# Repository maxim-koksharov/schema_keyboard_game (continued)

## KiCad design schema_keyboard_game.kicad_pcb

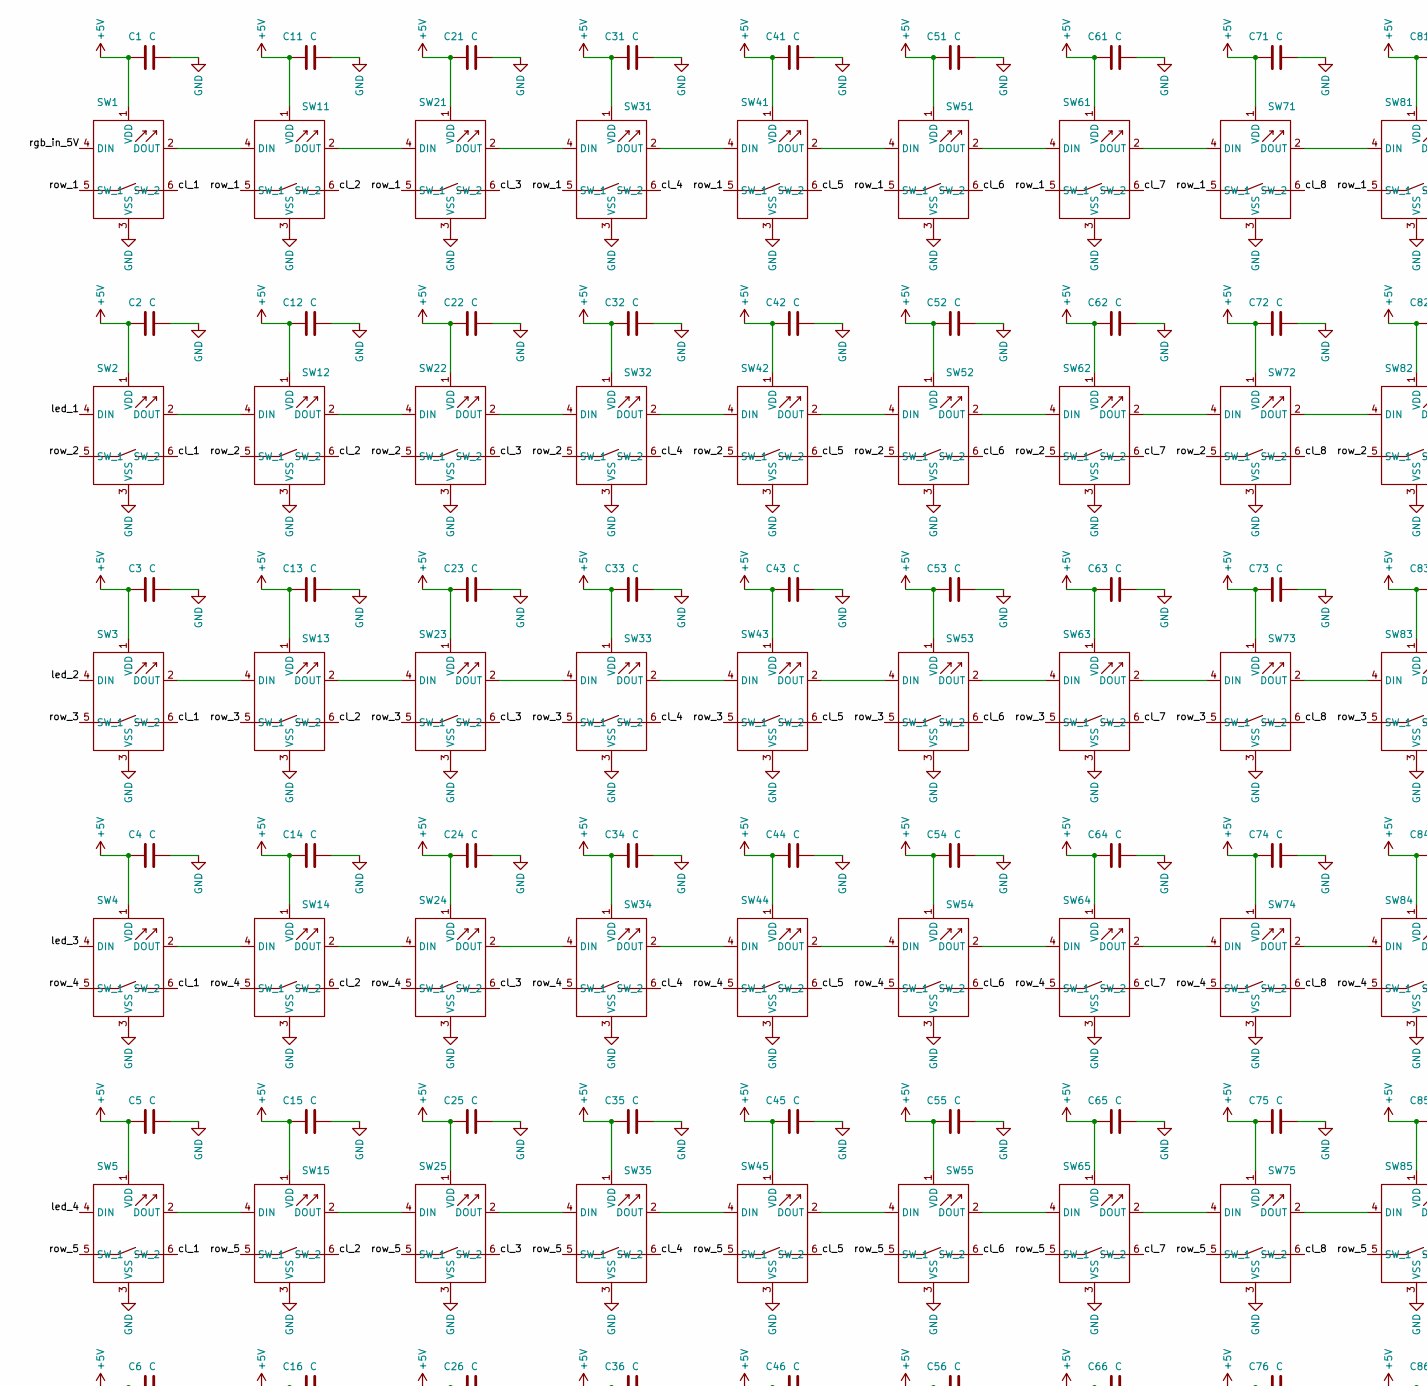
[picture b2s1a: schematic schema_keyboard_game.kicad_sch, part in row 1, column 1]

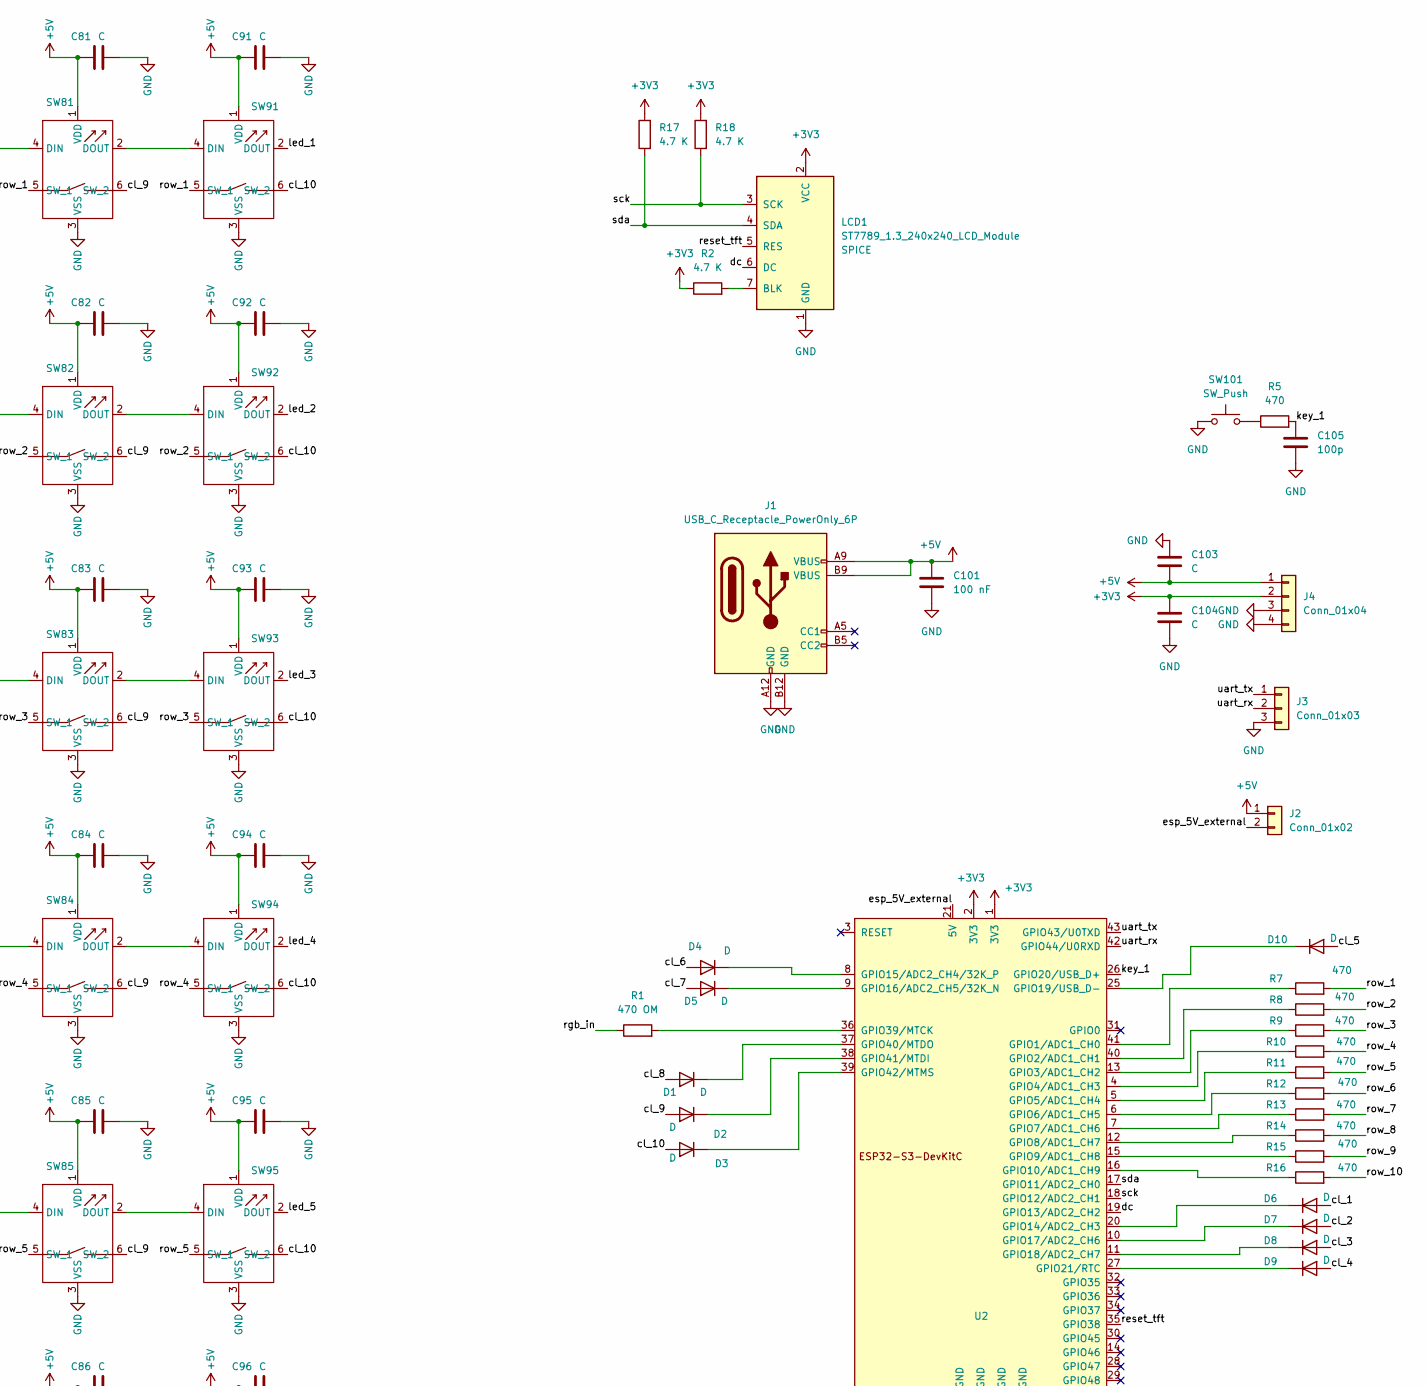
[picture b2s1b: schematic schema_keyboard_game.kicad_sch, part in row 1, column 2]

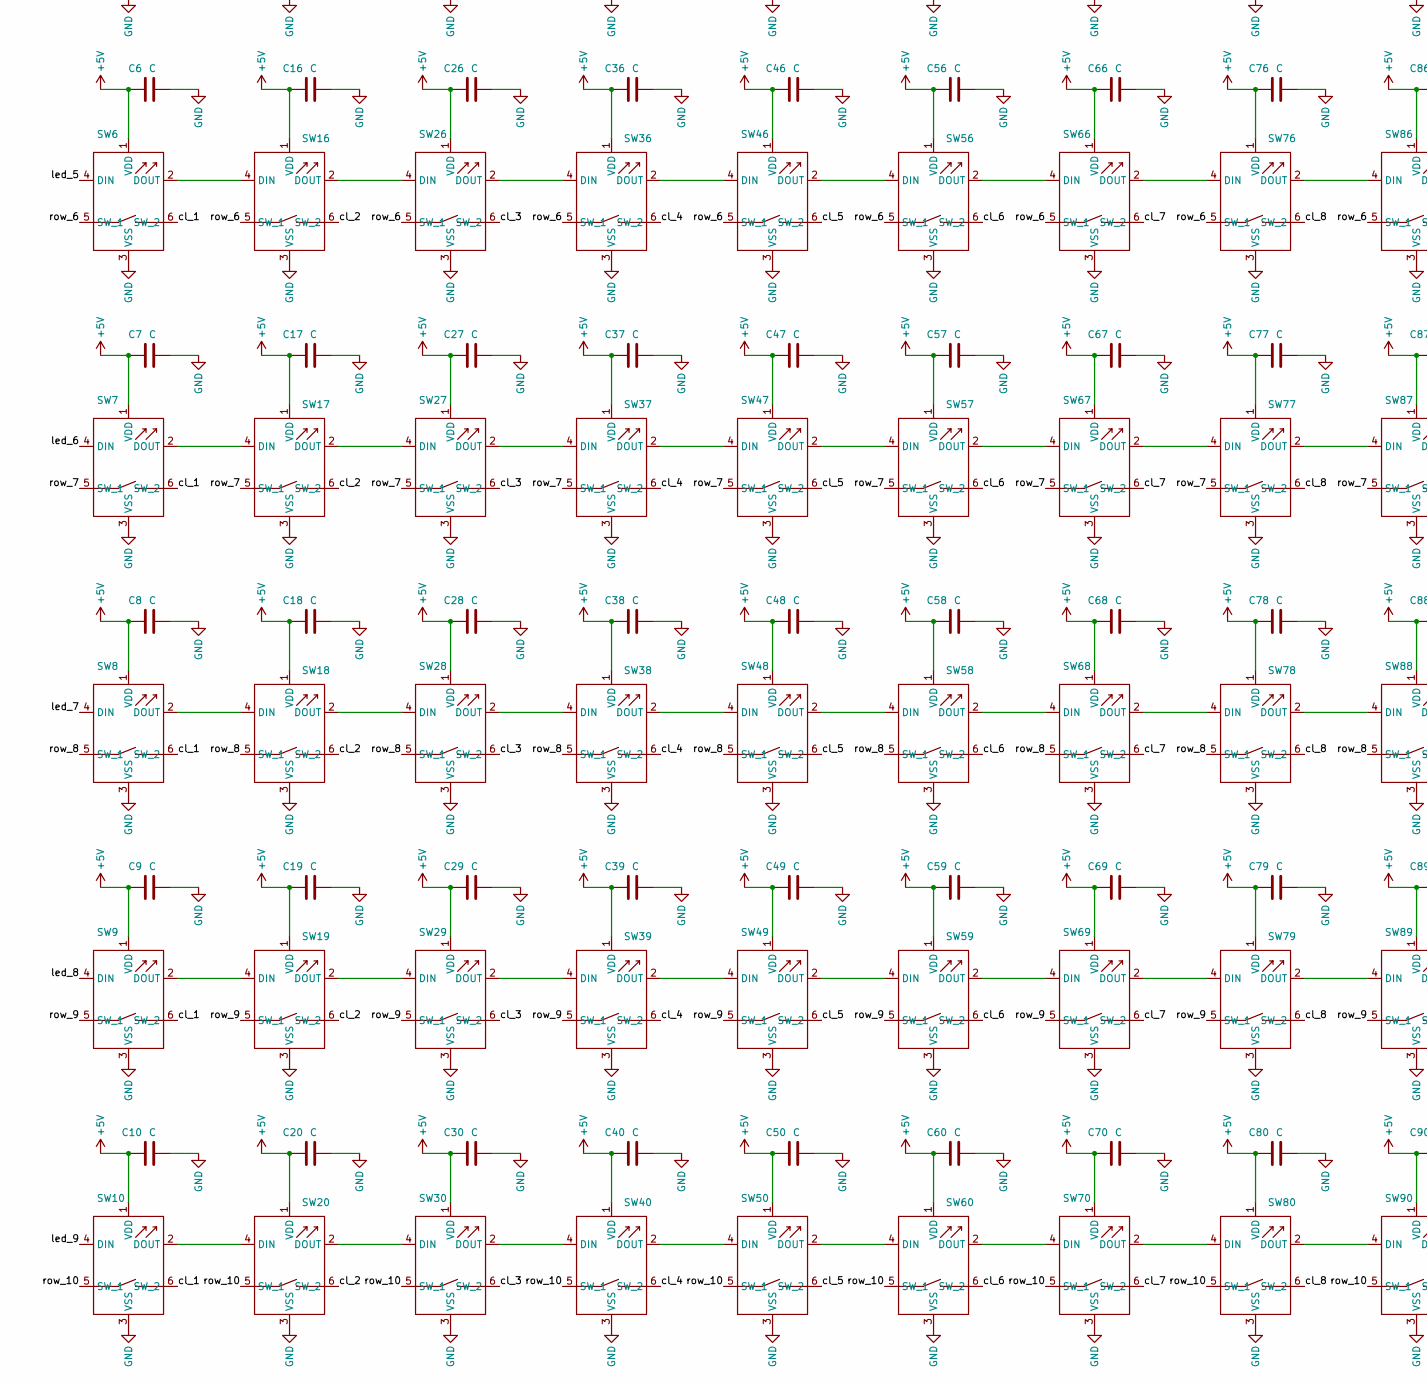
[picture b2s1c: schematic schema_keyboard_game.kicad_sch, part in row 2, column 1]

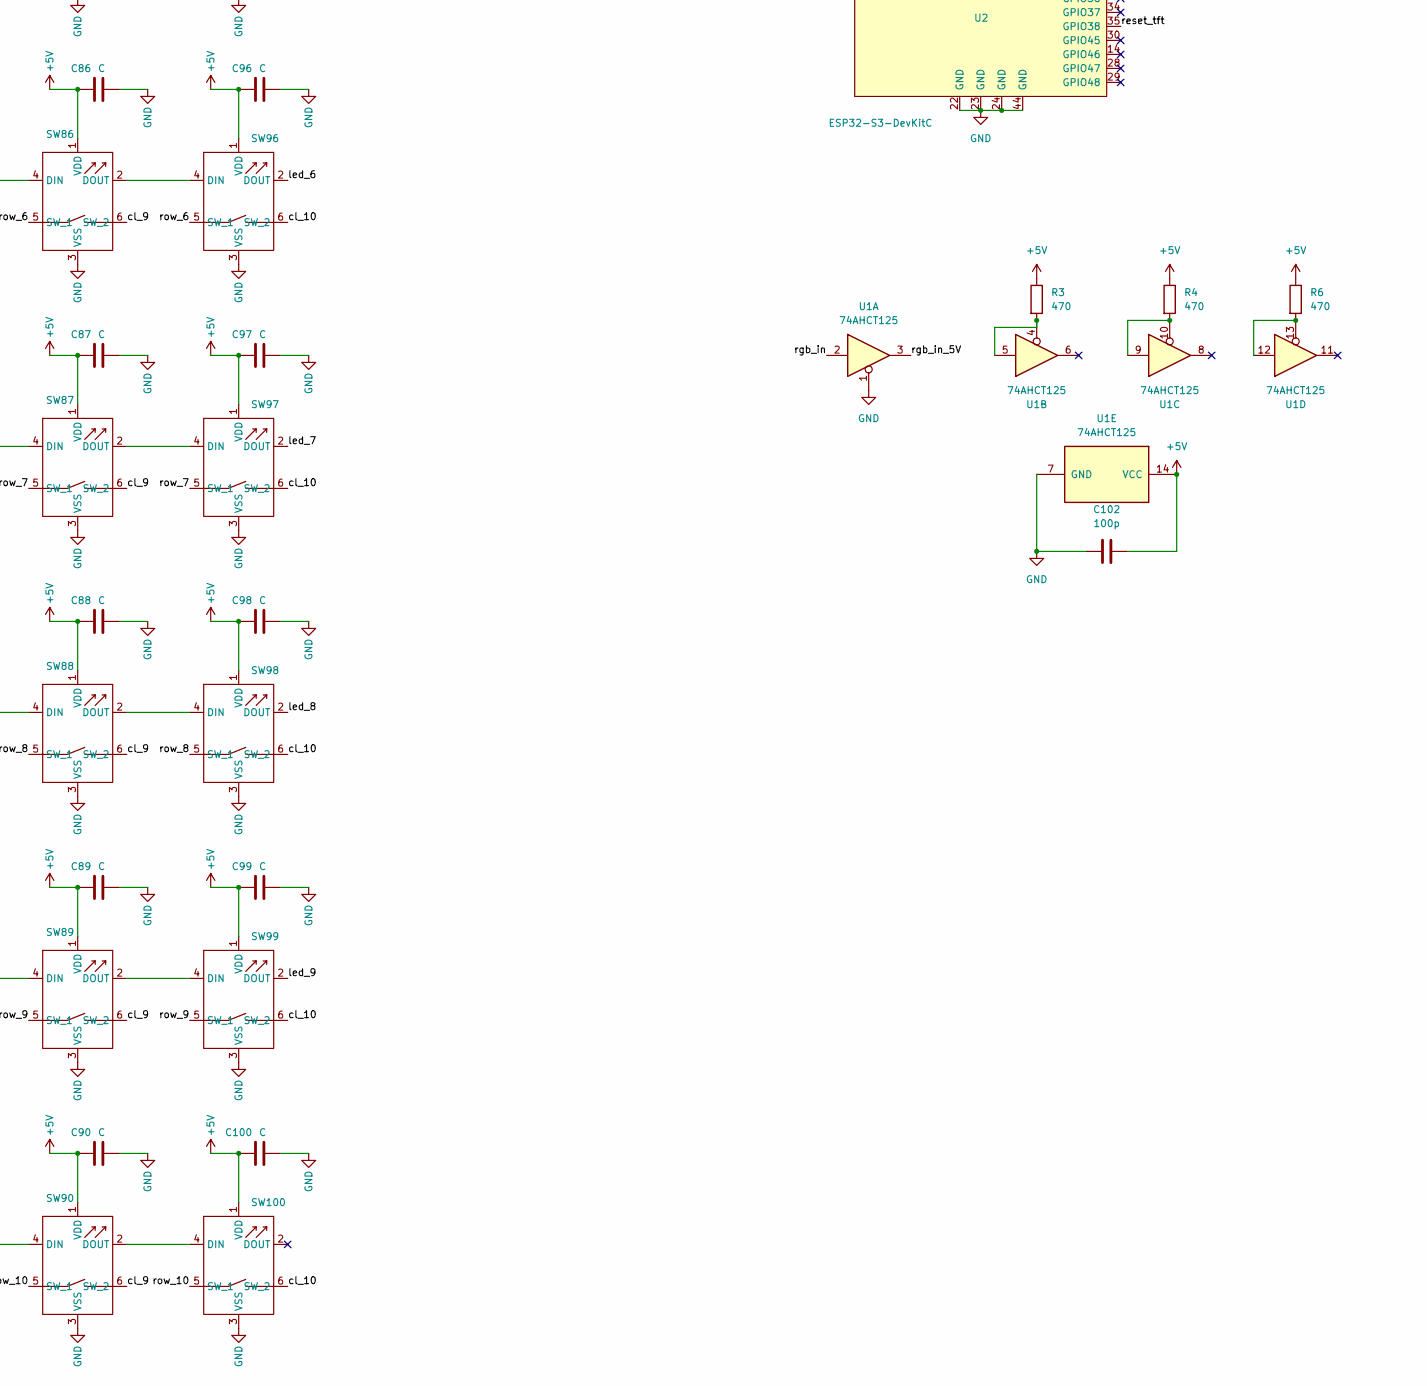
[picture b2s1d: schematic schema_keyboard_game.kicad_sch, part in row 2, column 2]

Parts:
C1, C2, C3, C4, C5, C6, C7, C8, C9, C10, C11, C12, C13, C14, C15, C16, C17, C18, C19, C20, C21, C22, C23, C24, C25, C26, C27, C28, C29, C30, C31, C32, C33, C34, C35, C36, C37, C38, C39, C40, C41, C42, C43, C44, C45, C46, C47, C48, C49, C50, C51, C52, C53, C54, C55, C56, C57, C58, C59, C60, C61, C62, C63, C64, C65, C66, C67, C68, C69, C70, C71, C72, C73, C74, C75, C76, C77, C78, C79, C80, C81, C82, C83, C84, C85, C86, C87, C88, C89, C90, C91, C92, C93, C94, C95, C96, C97, C98, C99, C100, C103, C104: C; C_1206_3216Metric
C101: 100 nF; C_1206_3216Metric
C102, C105: 100p; C_1206_3216Metric
D1, D2, D3, D4, D5, D6, D7, D8, D9, D10: D; D_SOD-123
J1: USB_C_Receptacle_PowerOnly_6P; USB_C_Receptacle_HRO_TYPE-C-31-M-17
J2: Conn_01x02; PinHeader_1x02_P2.54mm_Vertical
J3: Conn_01x03; PinHeader_1x03_P2.54mm_Vertical
J4: Conn_01x04; PinSocket_1x04_P2.54mm_Vertical
LCD1: ST7789_1.3_240x240_LCD_Module
R1: 470 OM; R_1206_3216Metric
R2, R17, R18: 4.7 K; R_1206_3216Metric
R3, R4, R5, R6, R7, R8, R9, R10, R11, R12, R13, R14, R15, R16: 470; R_1206_3216Metric
SW1, SW2, SW3, SW4, SW5, SW6, SW7, SW8, SW9, SW10, SW11, SW12, SW13, SW14, SW15, SW16, SW17, SW18, SW19, SW20, SW21, SW22, SW23, SW24, SW25, SW26, SW27, SW28, SW29, SW30, SW31, SW32, SW33, SW34, SW35, SW36, SW37, SW38, SW39, SW40, SW41, SW42, SW43, SW44, SW45, SW46, SW47, SW48, SW49, SW50, SW51, SW52, SW53, SW54, SW55, SW56, SW57, SW58, SW59, SW60, SW61, SW62, SW63, SW64, SW65, SW66, SW67, SW68, SW69, SW70, SW71, SW72, SW73, SW74, SW75, SW76, SW77, SW78, SW79, SW80, SW81, SW82, SW83, SW84, SW85, SW86, SW87, SW88, SW89, SW90, SW91, SW92, SW93, SW94, SW95, SW96, SW97, SW98, SW99, SW100: SW_Cherry_MX_LED_2
SW101: SW_Push; SW_PUSH_6mm
U1: 74AHCT125; DIP-14_W7.62mm
U2: ESP32-S3-DevKitC; ESP32-S3-DevKit_ALI

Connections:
+3V3: C104.1, J4.2, LCD1.2 (VCC), R2.1, R17.2, R18.2, U2.1 (3V3), U2.2 (3V3)
+5V: C1.1, C2.1, C3.1, C4.1, C5.1, C6.1, C7.1, C8.1, C9.1, C10.1, C11.1, C12.1, C13.1, C14.1, C15.1, C16.1, C17.1, C18.1, C19.1, C20.1, C21.1, C22.1, C23.1, C24.1, C25.1, C26.1, C27.1, C28.1, C29.1, C30.1, C31.1, C32.1, C33.1, C34.1, C35.1, C36.1, C37.1, C38.1, C39.1, C40.1, C41.1, C42.1, C43.1, C44.1, C45.1, C46.1, C47.1, C48.1, C49.1, C50.1, C51.1, C52.1, C53.1, C54.1, C55.1, C56.1, C57.1, C58.1, C59.1, C60.1, C61.1, C62.1, C63.1, C64.1, C65.1, C66.1, C67.1, C68.1, C69.1, C70.1, C71.1, C72.1, C73.1, C74.1, C75.1, C76.1, C77.1, C78.1, C79.1, C80.1, C81.1, C82.1, C83.1, C84.1, C85.1, C86.1, C87.1, C88.1, C89.1, C90.1, C91.1, C92.1, C93.1, C94.1, C95.1, C96.1, C97.1, C98.1, C99.1, C100.1, C101.1, C102.2, C103.2, J1.A9 (VBUS), J1.B9 (VBUS), J2.1, J4.1, R3.1, R4.1, R6.1, SW1.1 (VDD), SW2.1 (VDD), SW3.1 (VDD), SW4.1 (VDD), SW5.1 (VDD), SW6.1 (VDD), SW7.1 (VDD), SW8.1 (VDD), SW9.1 (VDD), SW10.1 (VDD), SW11.1 (VDD), SW12.1 (VDD), SW13.1 (VDD), SW14.1 (VDD), SW15.1 (VDD), SW16.1 (VDD), SW17.1 (VDD), SW18.1 (VDD), SW19.1 (VDD), SW20.1 (VDD), SW21.1 (VDD), SW22.1 (VDD), SW23.1 (VDD), SW24.1 (VDD), SW25.1 (VDD), SW26.1 (VDD), SW27.1 (VDD), SW28.1 (VDD), SW29.1 (VDD), SW30.1 (VDD), SW31.1 (VDD), SW32.1 (VDD), SW33.1 (VDD), SW34.1 (VDD), SW35.1 (VDD), SW36.1 (VDD), SW37.1 (VDD), SW38.1 (VDD), SW39.1 (VDD), SW40.1 (VDD), SW41.1 (VDD), SW42.1 (VDD), SW43.1 (VDD), SW44.1 (VDD), SW45.1 (VDD), SW46.1 (VDD), SW47.1 (VDD), SW48.1 (VDD), SW49.1 (VDD), SW50.1 (VDD), SW51.1 (VDD), SW52.1 (VDD), SW53.1 (VDD), SW54.1 (VDD), SW55.1 (VDD), SW56.1 (VDD), SW57.1 (VDD), SW58.1 (VDD), SW59.1 (VDD), SW60.1 (VDD), SW61.1 (VDD), SW62.1 (VDD), SW63.1 (VDD), SW64.1 (VDD), SW65.1 (VDD), SW66.1 (VDD), SW67.1 (VDD), SW68.1 (VDD), SW69.1 (VDD), SW70.1 (VDD), SW71.1 (VDD), SW72.1 (VDD), SW73.1 (VDD), SW74.1 (VDD), SW75.1 (VDD), SW76.1 (VDD), SW77.1 (VDD), SW78.1 (VDD), SW79.1 (VDD), SW80.1 (VDD), SW81.1 (VDD), SW82.1 (VDD), SW83.1 (VDD), SW84.1 (VDD), SW85.1 (VDD), SW86.1 (VDD), SW87.1 (VDD), SW88.1 (VDD), SW89.1 (VDD), SW90.1 (VDD), SW91.1 (VDD), SW92.1 (VDD), SW93.1 (VDD), SW94.1 (VDD), SW95.1 (VDD), SW96.1 (VDD), SW97.1 (VDD), SW98.1 (VDD), SW99.1 (VDD), SW100.1 (VDD), U1.14 (VCC)
/cl_1: D6.2 (A), SW1.6 (SW_2), SW2.6 (SW_2), SW3.6 (SW_2), SW4.6 (SW_2), SW5.6 (SW_2), SW6.6 (SW_2), SW7.6 (SW_2), SW8.6 (SW_2), SW9.6 (SW_2), SW10.6 (SW_2)
/cl_2: D7.2 (A), SW11.6 (SW_2), SW12.6 (SW_2), SW13.6 (SW_2), SW14.6 (SW_2), SW15.6 (SW_2), SW16.6 (SW_2), SW17.6 (SW_2), SW18.6 (SW_2), SW19.6 (SW_2), SW20.6 (SW_2)
/cl_3: D8.2 (A), SW21.6 (SW_2), SW22.6 (SW_2), SW23.6 (SW_2), SW24.6 (SW_2), SW25.6 (SW_2), SW26.6 (SW_2), SW27.6 (SW_2), SW28.6 (SW_2), SW29.6 (SW_2), SW30.6 (SW_2)
/cl_4: D9.2 (A), SW31.6 (SW_2), SW32.6 (SW_2), SW33.6 (SW_2), SW34.6 (SW_2), SW35.6 (SW_2), SW36.6 (SW_2), SW37.6 (SW_2), SW38.6 (SW_2), SW39.6 (SW_2), SW40.6 (SW_2)
/cl_5: D10.2 (A), SW41.6 (SW_2), SW42.6 (SW_2), SW43.6 (SW_2), SW44.6 (SW_2), SW45.6 (SW_2), SW46.6 (SW_2), SW47.6 (SW_2), SW48.6 (SW_2), SW49.6 (SW_2), SW50.6 (SW_2)
/cl_6: D4.2 (A), SW51.6 (SW_2), SW52.6 (SW_2), SW53.6 (SW_2), SW54.6 (SW_2), SW55.6 (SW_2), SW56.6 (SW_2), SW57.6 (SW_2), SW58.6 (SW_2), SW59.6 (SW_2), SW60.6 (SW_2)
/cl_7: D5.2 (A), SW61.6 (SW_2), SW62.6 (SW_2), SW63.6 (SW_2), SW64.6 (SW_2), SW65.6 (SW_2), SW66.6 (SW_2), SW67.6 (SW_2), SW68.6 (SW_2), SW69.6 (SW_2), SW70.6 (SW_2)
/cl_8: D1.2 (A), SW71.6 (SW_2), SW72.6 (SW_2), SW73.6 (SW_2), SW74.6 (SW_2), SW75.6 (SW_2), SW76.6 (SW_2), SW77.6 (SW_2), SW78.6 (SW_2), SW79.6 (SW_2), SW80.6 (SW_2)
/cl_9: D2.2 (A), SW81.6 (SW_2), SW82.6 (SW_2), SW83.6 (SW_2), SW84.6 (SW_2), SW85.6 (SW_2), SW86.6 (SW_2), SW87.6 (SW_2), SW88.6 (SW_2), SW89.6 (SW_2), SW90.6 (SW_2)
/cl_10: D3.2 (A), SW91.6 (SW_2), SW92.6 (SW_2), SW93.6 (SW_2), SW94.6 (SW_2), SW95.6 (SW_2), SW96.6 (SW_2), SW97.6 (SW_2), SW98.6 (SW_2), SW99.6 (SW_2), SW100.6 (SW_2)
/dc: LCD1.6 (DC), U2.19 (GPIO13/ADC2_CH2)
/esp_5V_external: J2.2, U2.21 (5V)
/key_1: C105.1, R5.2, U2.26 (GPIO20/USB_D+)
/led_1: SW2.4 (DIN), SW91.2 (DOUT)
/led_2: SW3.4 (DIN), SW92.2 (DOUT)
/led_3: SW4.4 (DIN), SW93.2 (DOUT)
/led_4: SW5.4 (DIN), SW94.2 (DOUT)
/led_5: SW6.4 (DIN), SW95.2 (DOUT)
/led_6: SW7.4 (DIN), SW96.2 (DOUT)
/led_7: SW8.4 (DIN), SW97.2 (DOUT)
/led_8: SW9.4 (DIN), SW98.2 (DOUT)
/led_9: SW10.4 (DIN), SW99.2 (DOUT)
/reset_tft: LCD1.5 (RES), U2.35 (GPIO38)
/rgb_in: R1.1, U1.2
/rgb_in_5V: SW1.4 (DIN), U1.3
/row_1: R7.2, SW1.5 (SW_1), SW11.5 (SW_1), SW21.5 (SW_1), SW31.5 (SW_1), SW41.5 (SW_1), SW51.5 (SW_1), SW61.5 (SW_1), SW71.5 (SW_1), SW81.5 (SW_1), SW91.5 (SW_1)
/row_2: R8.2, SW2.5 (SW_1), SW12.5 (SW_1), SW22.5 (SW_1), SW32.5 (SW_1), SW42.5 (SW_1), SW52.5 (SW_1), SW62.5 (SW_1), SW72.5 (SW_1), SW82.5 (SW_1), SW92.5 (SW_1)
/row_3: R9.2, SW3.5 (SW_1), SW13.5 (SW_1), SW23.5 (SW_1), SW33.5 (SW_1), SW43.5 (SW_1), SW53.5 (SW_1), SW63.5 (SW_1), SW73.5 (SW_1), SW83.5 (SW_1), SW93.5 (SW_1)
/row_4: R10.2, SW4.5 (SW_1), SW14.5 (SW_1), SW24.5 (SW_1), SW34.5 (SW_1), SW44.5 (SW_1), SW54.5 (SW_1), SW64.5 (SW_1), SW74.5 (SW_1), SW84.5 (SW_1), SW94.5 (SW_1)
/row_5: R11.2, SW5.5 (SW_1), SW15.5 (SW_1), SW25.5 (SW_1), SW35.5 (SW_1), SW45.5 (SW_1), SW55.5 (SW_1), SW65.5 (SW_1), SW75.5 (SW_1), SW85.5 (SW_1), SW95.5 (SW_1)
/row_6: R12.2, SW6.5 (SW_1), SW16.5 (SW_1), SW26.5 (SW_1), SW36.5 (SW_1), SW46.5 (SW_1), SW56.5 (SW_1), SW66.5 (SW_1), SW76.5 (SW_1), SW86.5 (SW_1), SW96.5 (SW_1)
/row_7: R13.2, SW7.5 (SW_1), SW17.5 (SW_1), SW27.5 (SW_1), SW37.5 (SW_1), SW47.5 (SW_1), SW57.5 (SW_1), SW67.5 (SW_1), SW77.5 (SW_1), SW87.5 (SW_1), SW97.5 (SW_1)
/row_8: R14.2, SW8.5 (SW_1), SW18.5 (SW_1), SW28.5 (SW_1), SW38.5 (SW_1), SW48.5 (SW_1), SW58.5 (SW_1), SW68.5 (SW_1), SW78.5 (SW_1), SW88.5 (SW_1), SW98.5 (SW_1)
/row_9: R15.2, SW9.5 (SW_1), SW19.5 (SW_1), SW29.5 (SW_1), SW39.5 (SW_1), SW49.5 (SW_1), SW59.5 (SW_1), SW69.5 (SW_1), SW79.5 (SW_1), SW89.5 (SW_1), SW99.5 (SW_1)
/row_10: R16.2, SW10.5 (SW_1), SW20.5 (SW_1), SW30.5 (SW_1), SW40.5 (SW_1), SW50.5 (SW_1), SW60.5 (SW_1), SW70.5 (SW_1), SW80.5 (SW_1), SW90.5 (SW_1), SW100.5 (SW_1)
/sck: LCD1.3 (SCK), R18.1, U2.18 (GPIO12/ADC2_CH1)
/sda: LCD1.4 (SDA), R17.1, U2.17 (GPIO11/ADC2_CH0)
/uart_rx: J3.2, U2.42 (GPIO44/U0RXD)
/uart_tx: J3.1, U2.43 (GPIO43/U0TXD)
GND: C1.2, C2.2, C3.2, C4.2, C5.2, C6.2, C7.2, C8.2, C9.2, C10.2, C11.2, C12.2, C13.2, C14.2, C15.2, C16.2, C17.2, C18.2, C19.2, C20.2, C21.2, C22.2, C23.2, C24.2, C25.2, C26.2, C27.2, C28.2, C29.2, C30.2, C31.2, C32.2, C33.2, C34.2, C35.2, C36.2, C37.2, C38.2, C39.2, C40.2, C41.2, C42.2, C43.2, C44.2, C45.2, C46.2, C47.2, C48.2, C49.2, C50.2, C51.2, C52.2, C53.2, C54.2, C55.2, C56.2, C57.2, C58.2, C59.2, C60.2, C61.2, C62.2, C63.2, C64.2, C65.2, C66.2, C67.2, C68.2, C69.2, C70.2, C71.2, C72.2, C73.2, C74.2, C75.2, C76.2, C77.2, C78.2, C79.2, C80.2, C81.2, C82.2, C83.2, C84.2, C85.2, C86.2, C87.2, C88.2, C89.2, C90.2, C91.2, C92.2, C93.2, C94.2, C95.2, C96.2, C97.2, C98.2, C99.2, C100.2, C101.2, C102.1, C103.1, C104.2, C105.2, J1.A12 (GND), J1.B12 (GND), J3.3, J4.3, J4.4, LCD1.1 (GND), SW1.3 (VSS), SW2.3 (VSS), SW3.3 (VSS), SW4.3 (VSS), SW5.3 (VSS), SW6.3 (VSS), SW7.3 (VSS), SW8.3 (VSS), SW9.3 (VSS), SW10.3 (VSS), SW11.3 (VSS), SW12.3 (VSS), SW13.3 (VSS), SW14.3 (VSS), SW15.3 (VSS), SW16.3 (VSS), SW17.3 (VSS), SW18.3 (VSS), SW19.3 (VSS), SW20.3 (VSS), SW21.3 (VSS), SW22.3 (VSS), SW23.3 (VSS), SW24.3 (VSS), SW25.3 (VSS), SW26.3 (VSS), SW27.3 (VSS), SW28.3 (VSS), SW29.3 (VSS), SW30.3 (VSS), SW31.3 (VSS), SW32.3 (VSS), SW33.3 (VSS), SW34.3 (VSS), SW35.3 (VSS), SW36.3 (VSS), SW37.3 (VSS), SW38.3 (VSS), SW39.3 (VSS), SW40.3 (VSS), SW41.3 (VSS), SW42.3 (VSS), SW43.3 (VSS), SW44.3 (VSS), SW45.3 (VSS), SW46.3 (VSS), SW47.3 (VSS), SW48.3 (VSS), SW49.3 (VSS), SW50.3 (VSS), SW51.3 (VSS), SW52.3 (VSS), SW53.3 (VSS), SW54.3 (VSS), SW55.3 (VSS), SW56.3 (VSS), SW57.3 (VSS), SW58.3 (VSS), SW59.3 (VSS), SW60.3 (VSS), SW61.3 (VSS), SW62.3 (VSS), SW63.3 (VSS), SW64.3 (VSS), SW65.3 (VSS), SW66.3 (VSS), SW67.3 (VSS), SW68.3 (VSS), SW69.3 (VSS), SW70.3 (VSS), SW71.3 (VSS), SW72.3 (VSS), SW73.3 (VSS), SW74.3 (VSS), SW75.3 (VSS), SW76.3 (VSS), SW77.3 (VSS), SW78.3 (VSS), SW79.3 (VSS), SW80.3 (VSS), SW81.3 (VSS), SW82.3 (VSS), SW83.3 (VSS), SW84.3 (VSS), SW85.3 (VSS), SW86.3 (VSS), SW87.3 (VSS), SW88.3 (VSS), SW89.3 (VSS), SW90.3 (VSS), SW91.3 (VSS), SW92.3 (VSS), SW93.3 (VSS), SW94.3 (VSS), SW95.3 (VSS), SW96.3 (VSS), SW97.3 (VSS), SW98.3 (VSS), SW99.3 (VSS), SW100.3 (VSS), SW101.1, U1.1, U1.7 (GND), U2.22 (GND), U2.23 (GND), U2.24 (GND), U2.44 (GND)
unnamed: D1.1 (K), U2.37 (GPIO40/MTDO)
unnamed: D2.1 (K), U2.38 (GPIO41/MTDI)
unnamed: D3.1 (K), U2.39 (GPIO42/MTMS)
unnamed: D4.1 (K), U2.8 (GPIO15/ADC2_CH4/32K_P)
unnamed: D5.1 (K), U2.9 (GPIO16/ADC2_CH5/32K_N)
unnamed: D6.1 (K), U2.20 (GPIO14/ADC2_CH3)
unnamed: D7.1 (K), U2.10 (GPIO17/ADC2_CH6)
unnamed: D8.1 (K), U2.11 (GPIO18/ADC2_CH7)
unnamed: D9.1 (K), U2.27 (GPIO21/RTC)
unnamed: D10.1 (K), U2.25 (GPIO19/USB_D-)
unnamed: LCD1.7 (BLK), R2.2
unnamed: R3.2, U1.4, U1.5
unnamed: R4.2, U1.9, U1.10
unnamed: R5.1, SW101.2
unnamed: R6.2, U1.12, U1.13
unnamed: SW1.2 (DOUT), SW11.4 (DIN)
unnamed: SW10.2 (DOUT), SW20.4 (DIN)
unnamed: SW11.2 (DOUT), SW21.4 (DIN)
unnamed: SW2.2 (DOUT), SW12.4 (DIN)
unnamed: SW12.2 (DOUT), SW22.4 (DIN)
unnamed: SW3.2 (DOUT), SW13.4 (DIN)
unnamed: SW13.2 (DOUT), SW23.4 (DIN)
unnamed: SW4.2 (DOUT), SW14.4 (DIN)
unnamed: SW14.2 (DOUT), SW24.4 (DIN)
unnamed: SW5.2 (DOUT), SW15.4 (DIN)
unnamed: SW15.2 (DOUT), SW25.4 (DIN)
unnamed: SW6.2 (DOUT), SW16.4 (DIN)
unnamed: SW16.2 (DOUT), SW26.4 (DIN)
unnamed: SW7.2 (DOUT), SW17.4 (DIN)
unnamed: SW17.2 (DOUT), SW27.4 (DIN)
unnamed: SW8.2 (DOUT), SW18.4 (DIN)
unnamed: SW18.2 (DOUT), SW28.4 (DIN)
unnamed: SW9.2 (DOUT), SW19.4 (DIN)
unnamed: SW19.2 (DOUT), SW29.4 (DIN)
unnamed: SW20.2 (DOUT), SW30.4 (DIN)
unnamed: SW21.2 (DOUT), SW31.4 (DIN)
unnamed: SW22.2 (DOUT), SW32.4 (DIN)
unnamed: SW23.2 (DOUT), SW33.4 (DIN)
unnamed: SW24.2 (DOUT), SW34.4 (DIN)
unnamed: SW25.2 (DOUT), SW35.4 (DIN)
unnamed: SW26.2 (DOUT), SW36.4 (DIN)
unnamed: SW27.2 (DOUT), SW37.4 (DIN)
unnamed: SW28.2 (DOUT), SW38.4 (DIN)
unnamed: SW29.2 (DOUT), SW39.4 (DIN)
unnamed: SW30.2 (DOUT), SW40.4 (DIN)
unnamed: SW31.2 (DOUT), SW41.4 (DIN)
unnamed: SW32.2 (DOUT), SW42.4 (DIN)
unnamed: SW33.2 (DOUT), SW43.4 (DIN)
unnamed: SW34.2 (DOUT), SW44.4 (DIN)
unnamed: SW35.2 (DOUT), SW45.4 (DIN)
unnamed: SW36.2 (DOUT), SW46.4 (DIN)
unnamed: SW37.2 (DOUT), SW47.4 (DIN)
unnamed: SW38.2 (DOUT), SW48.4 (DIN)
unnamed: SW39.2 (DOUT), SW49.4 (DIN)
unnamed: SW40.2 (DOUT), SW50.4 (DIN)
unnamed: SW41.2 (DOUT), SW51.4 (DIN)
unnamed: SW42.2 (DOUT), SW52.4 (DIN)
unnamed: SW43.2 (DOUT), SW53.4 (DIN)
unnamed: SW44.2 (DOUT), SW54.4 (DIN)
unnamed: SW45.2 (DOUT), SW55.4 (DIN)
unnamed: SW46.2 (DOUT), SW56.4 (DIN)
unnamed: SW47.2 (DOUT), SW57.4 (DIN)
unnamed: SW48.2 (DOUT), SW58.4 (DIN)
unnamed: SW49.2 (DOUT), SW59.4 (DIN)
unnamed: SW50.2 (DOUT), SW60.4 (DIN)
unnamed: SW51.2 (DOUT), SW61.4 (DIN)
unnamed: SW52.2 (DOUT), SW62.4 (DIN)
unnamed: SW53.2 (DOUT), SW63.4 (DIN)
unnamed: SW54.2 (DOUT), SW64.4 (DIN)
unnamed: SW55.2 (DOUT), SW65.4 (DIN)
unnamed: SW56.2 (DOUT), SW66.4 (DIN)
unnamed: SW57.2 (DOUT), SW67.4 (DIN)
unnamed: SW58.2 (DOUT), SW68.4 (DIN)
unnamed: SW59.2 (DOUT), SW69.4 (DIN)
unnamed: SW60.2 (DOUT), SW70.4 (DIN)
unnamed: SW61.2 (DOUT), SW71.4 (DIN)
unnamed: SW62.2 (DOUT), SW72.4 (DIN)
unnamed: SW63.2 (DOUT), SW73.4 (DIN)
unnamed: SW64.2 (DOUT), SW74.4 (DIN)
unnamed: SW65.2 (DOUT), SW75.4 (DIN)
unnamed: SW66.2 (DOUT), SW76.4 (DIN)
unnamed: SW67.2 (DOUT), SW77.4 (DIN)
unnamed: SW68.2 (DOUT), SW78.4 (DIN)
unnamed: SW69.2 (DOUT), SW79.4 (DIN)
unnamed: SW70.2 (DOUT), SW80.4 (DIN)
unnamed: SW71.2 (DOUT), SW81.4 (DIN)
unnamed: SW72.2 (DOUT), SW82.4 (DIN)
unnamed: SW73.2 (DOUT), SW83.4 (DIN)
unnamed: SW74.2 (DOUT), SW84.4 (DIN)
unnamed: SW75.2 (DOUT), SW85.4 (DIN)
unnamed: SW76.2 (DOUT), SW86.4 (DIN)
unnamed: SW77.2 (DOUT), SW87.4 (DIN)
unnamed: SW78.2 (DOUT), SW88.4 (DIN)
unnamed: SW79.2 (DOUT), SW89.4 (DIN)
unnamed: SW80.2 (DOUT), SW90.4 (DIN)
unnamed: SW81.2 (DOUT), SW91.4 (DIN)
unnamed: SW82.2 (DOUT), SW92.4 (DIN)
unnamed: SW83.2 (DOUT), SW93.4 (DIN)
unnamed: SW84.2 (DOUT), SW94.4 (DIN)
unnamed: SW85.2 (DOUT), SW95.4 (DIN)
unnamed: SW86.2 (DOUT), SW96.4 (DIN)
unnamed: SW87.2 (DOUT), SW97.4 (DIN)
unnamed: SW88.2 (DOUT), SW98.4 (DIN)
unnamed: SW89.2 (DOUT), SW99.4 (DIN)
unnamed: SW90.2 (DOUT), SW100.4 (DIN)
unnamed: R7.1, U2.41 (GPIO1/ADC1_CH0)
unnamed: R8.1, U2.40 (GPIO2/ADC1_CH1)
unnamed: R9.1, U2.13 (GPIO3/ADC1_CH2)
unnamed: R10.1, U2.4 (GPIO4/ADC1_CH3)
unnamed: R11.1, U2.5 (GPIO5/ADC1_CH4)
unnamed: R12.1, U2.6 (GPIO6/ADC1_CH5)
unnamed: R13.1, U2.7 (GPIO7/ADC1_CH6)
unnamed: R14.1, U2.12 (GPIO8/ADC1_CH7)
unnamed: R15.1, U2.15 (GPIO9/ADC1_CH8)
unnamed: R16.1, U2.16 (GPIO10/ADC1_CH9)
unnamed: R1.2, U2.36 (GPIO39/MTCK)

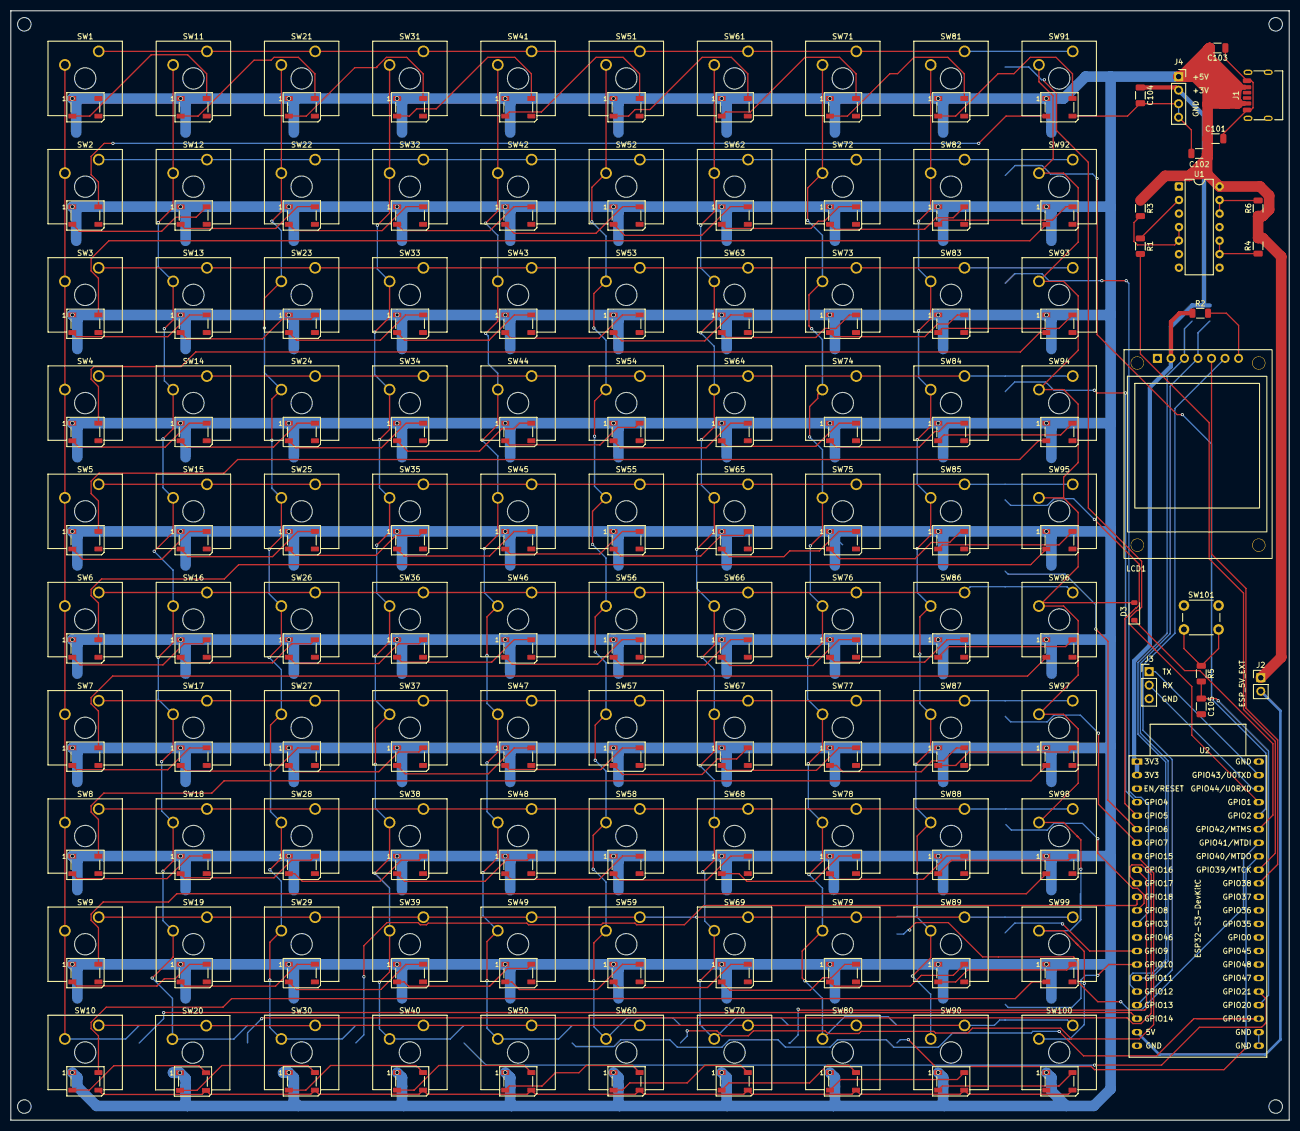
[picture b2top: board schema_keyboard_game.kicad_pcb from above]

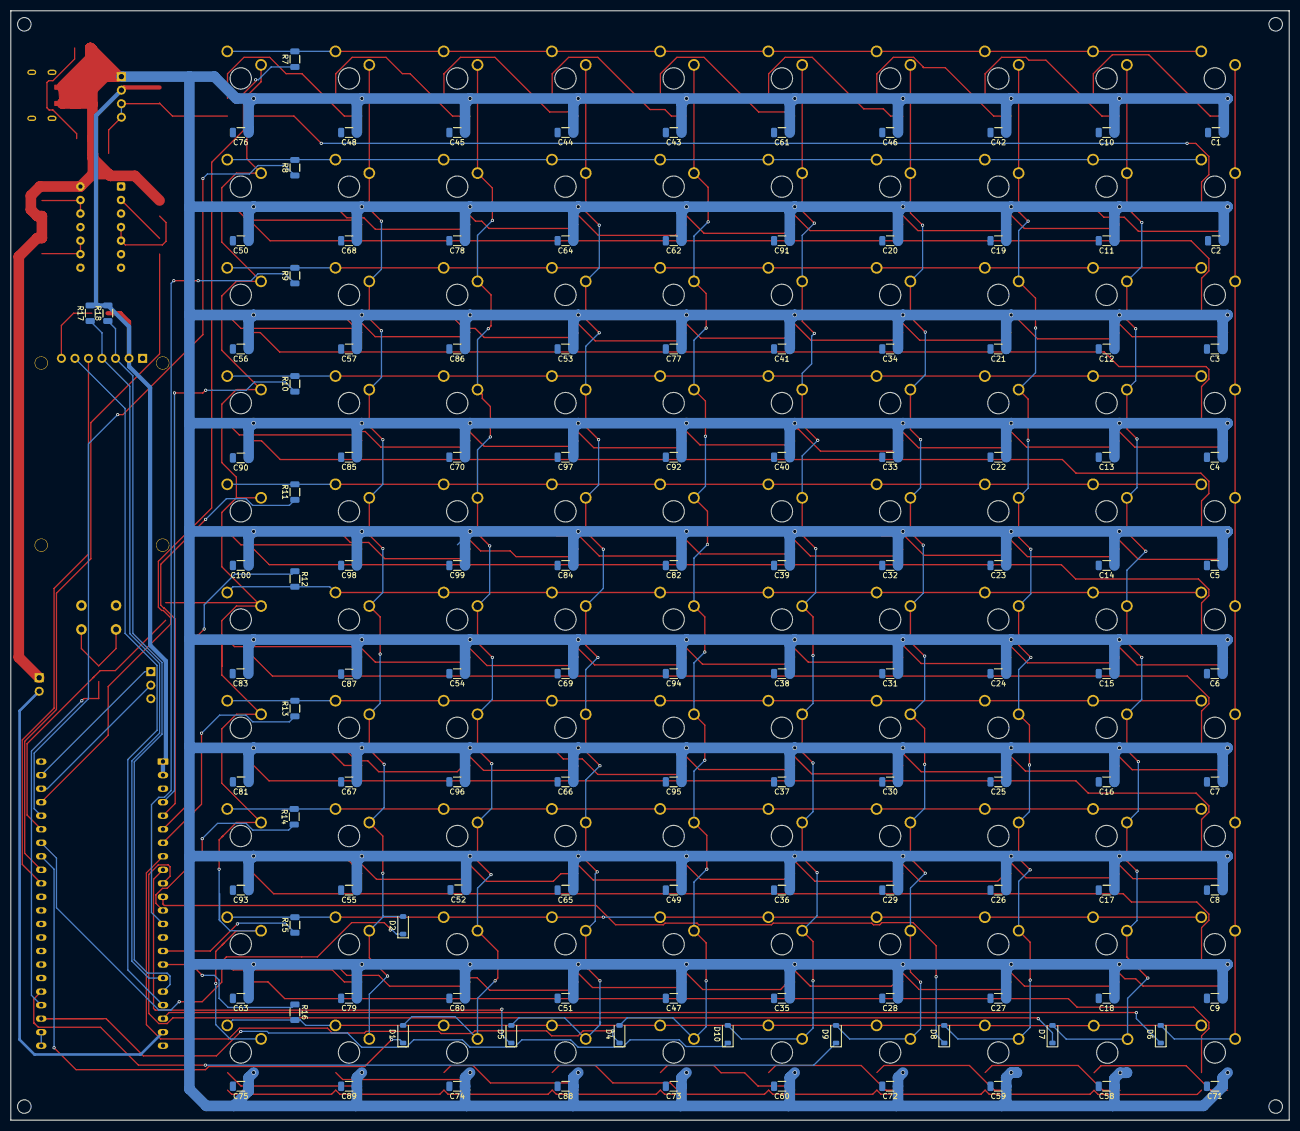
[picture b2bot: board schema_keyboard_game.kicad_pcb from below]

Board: 2 copper layers, 240.0 x 208.3 mm, 241 parts (121 on the bottom side), 158 nets.

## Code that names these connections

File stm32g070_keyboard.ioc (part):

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Mcu.Name=STM32G070RBTx
Mcu.Package=LQFP64
Mcu.UserName=STM32G070RBTx
PA10.Mode=Asynchronous
PA10.Signal=USART1_RX
PA11\ [PA9].GPIOParameters=GPIO_Label
PA11\ [PA9].GPIO_Label=audio_mode
PA11\ [PA9].Signal=GPIO_Output
PA12\ [PA10].Mode=Half_Duplex_Master
PA12\ [PA10].Signal=I2S1_SD
PA13.Mode=Serial_Wire
PA13.Signal=SYS_SWDIO
PA14-BOOT0.Mode=Serial_Wire
PA14-BOOT0.Signal=SYS_SWCLK
PA15.Mode=Half_Duplex_Master
PA15.Signal=I2S1_WS
PA8.GPIOParameters=GPIO_Label
PA8.GPIO_Label=SPI_CS
PA8.Signal=GPIO_Output
PA9.Mode=Asynchronous
PA9.Signal=USART1_TX
PB13.Mode=Full_Duplex_Master
PB13.Signal=SPI2_SCK
PB14.Mode=Full_Duplex_Master
PB14.Signal=SPI2_MISO
PB15.Mode=Full_Duplex_Master
PB15.Signal=SPI2_MOSI
PD8.Mode=Half_Duplex_Master
PD8.Signal=I2S1_CK
PF0-OSC_IN\ (PF0).Mode=HSE-External-Clock-Source
PF0-OSC_IN\ (PF0).Signal=RCC_OSC_IN
RCC.HSE_VALUE=8000000
RCC.SYSCLKFreq_VALUE=16000000
board=custom
